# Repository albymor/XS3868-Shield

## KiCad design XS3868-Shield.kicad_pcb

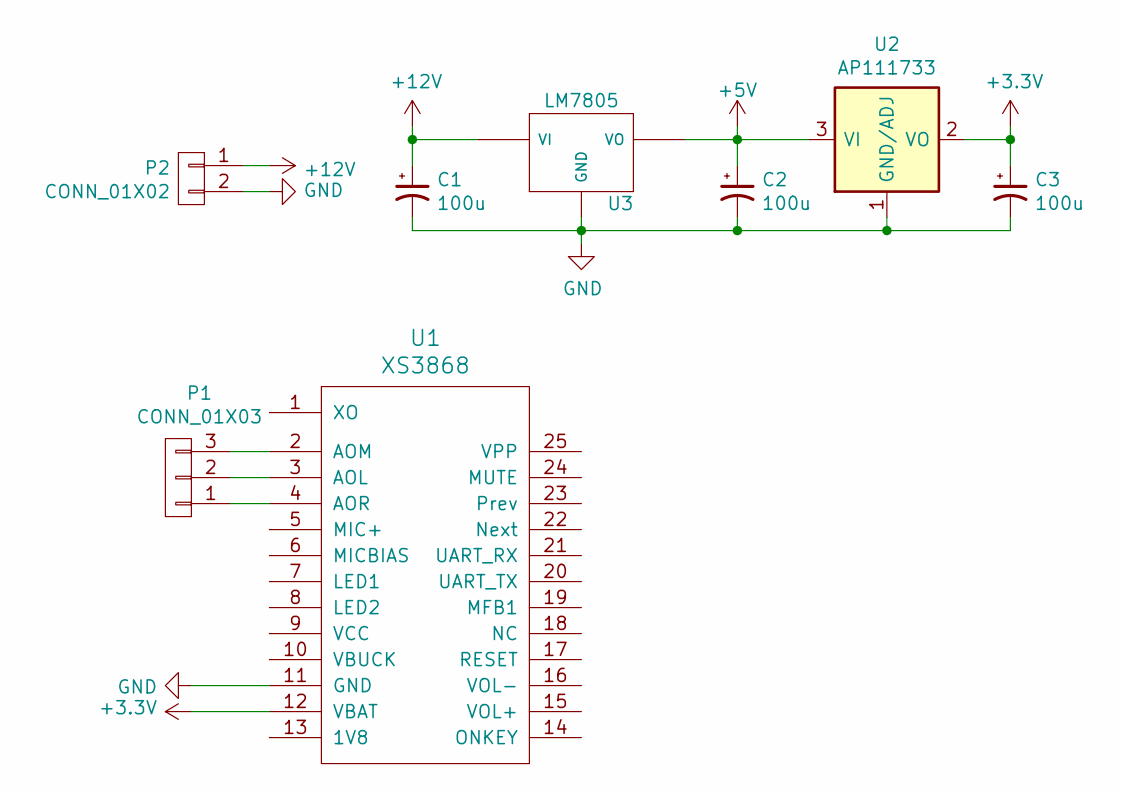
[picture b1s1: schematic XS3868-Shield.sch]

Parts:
C1, C2, C3: 100u; SMD-2512_Pol
P1: CONN_01X03; Pin_Header_Straight_1x03_Pitch2.54mm
P2: CONN_01X02; Pin_Header_Straight_1x02_Pitch2.54mm
U1: XS3868; XS3868_Module
U2: AP111733; SOT-223
U3: LM7805; LM7805_TO92

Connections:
+3V3: C3.1, U1.12 (VBAT), U2.2 (VO), U2.4 (VO)
+5V: C2.1, U2.3 (VI), U3.VO
+12V: C1.1, P2.1, U3.VI
GND: C1.2, C2.2, C3.2, P2.2, U1.11 (GND), U2.1 (GND/ADJ), U3.GND
unnamed: P1.1, U1.4 (AOR)
unnamed: P1.2, U1.3 (AOL)
unnamed: P1.3, U1.2 (AOM)

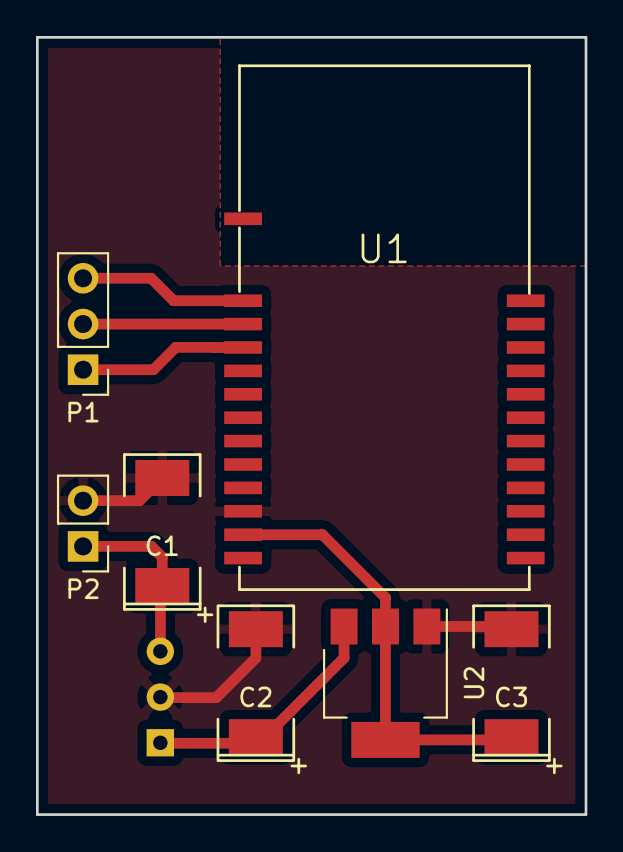
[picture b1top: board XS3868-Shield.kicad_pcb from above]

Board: 2 copper layers, 30.5 x 43.2 mm, 8 parts (1 on the bottom side), 7 nets.

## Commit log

2017-02-23 PCB done
2017-03-10 Added ground plane
2017-03-10 Layout review
